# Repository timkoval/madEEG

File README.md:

# madEEG

This project is a fork and rebirth of an old project called "[OpenEEG](http://openeeg.sourceforge.net/doc/)".

The main feature of this project is that it uses currently available SMD components. Moreover, in the future I'm planning to try to make it cheaper using DSP instead of amplifier filters where it is possible.

I wanted to make it myself as a pet project, but unfortunately I don't have enough time and money. However, I really want this project to be developed... You are welcome to contribute!

## Requirements and tools

Schematic and PCB - [KiCAD](https://kicad-pcb.org/) 

Firmware - [STM32CubeIDE](https://www.st.com/en/development-tools/stm32cubeide.html) or any other IDE/code editor (As for me, I've recently migrated from CubeIDE to [VSCodium](https://vscodium.com/))

 Software - haven't thought about it yet, open to suggestions.

## Installation

No need to install project, just clone it, develop and contribute :) 

## Contributing

Pull requests are welcome! For major changes, please open an issue first to discuss what you would like to change.

## Authors

- **Tim Koval** - *Initial work* - [madTRACER](https://github.com/madTRACER)

## License

This project is under the MIT license.

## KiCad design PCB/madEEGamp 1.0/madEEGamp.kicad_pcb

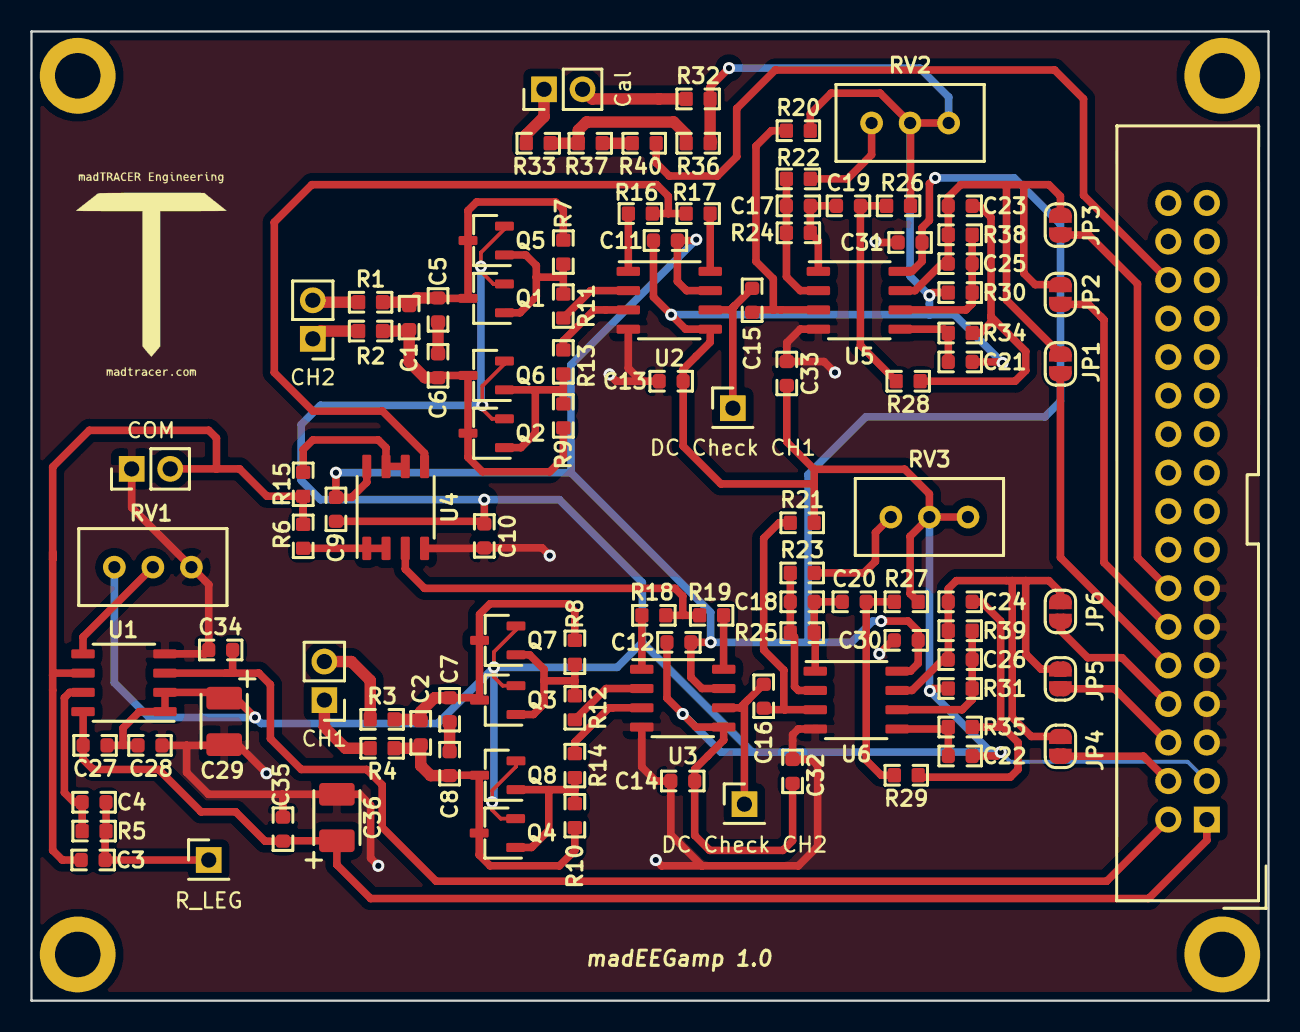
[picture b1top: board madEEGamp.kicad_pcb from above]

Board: 2 copper layers, 81.5 x 63.9 mm, 107 parts (0 on the bottom side), 66 nets.

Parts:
C1, C2: 10pF; C_0603
C3, C4, C17, C18, C25, C26: 1nF; C_0603
C5, C6, C7, C8: 100pF; C_0603
C9, C10, C11, C12, C13, C14, C27, C28, C30, C31, C32, C33: 100nF; C_0603
C15, C16, C19, C20: 1μF; C_0603
C21, C22: 220nF 5%; C_0603
C23, C24: 33nF 5%; C_0603
C29: 47μF tan 1ohm; CP_EIA-3528-15_AVX-H
C34, C35: 10nF; C_0603
C36: 47μF; CP_EIA-3528-15_AVX-H
CH1: CH1; PinHeader_1x02_P2.54mm_Vertical
CH2: CH2; PinHeader_1x02_P2.54mm_Vertical
COM: COM; PinHeader_1x02_P2.54mm_Vertical
Cal: Cal; PinHeader_1x02_P2.54mm_Vertical
DC Check CH1: DC Check CH1; PinHeader_1x01_P2.54mm_Vertical
DC Check CH2: DC Check CH2; PinHeader_1x01_P2.54mm_Vertical
JP1, JP4: SJ201; SolderJumper-2_P1.3mm_Open_RoundedPad1.0x1.5mm
JP2, JP5: SJ202; SolderJumper-2_P1.3mm_Open_RoundedPad1.0x1.5mm
JP3, JP6: SJ203; SolderJumper-2_P1.3mm_Open_RoundedPad1.0x1.5mm
Q1, Q2, Q3, Q4: BC847; SOT-23
Q5, Q6, Q7, Q8: BC857; SOT-23
R1, R2, R3, R4, R7, R8, R9, R10, R11, R12, R13, R14, R16, R17, R18, R19: 2k2; R_0603
R5: 200k; R_0603
R6, R15, R28, R29, R32, R33: 10k; R_0603
R20, R21, R26, R27, R37, R40: 1M; R_0603
R22, R23: 1k; R_0603
R24, R25, R38, R39: 100k; R_0603
R30, R31: 8.2k; R_0603
R34, R35: 15k; R_0603
R36: 100; R_0603
RV1, RV2, RV3: 20k; BOURNS_3296W_Vertical
R_LEG: R_LEG; PinHeader_1x01_P2.54mm_Vertical
U1, U4, U5, U6: AD822; SOIC-8_3.9x4.9mm_P1.27mm
U2, U3: AD620; SOIC-8_3.9x4.9mm_P1.27mm
X7: PIN_HEADER_2X17_2.54; IDC-Header_2x17_P2.54mm_Vertical

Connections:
+5V: C9.2, C11.1, C12.1, C30.1, C31.1, U2.7, U3.7, U4.8, U5.8, U6.8
/ADIN0: C24.1, C26.1, JP4.2, JP5.2, JP6.2, R39.1, U6.7
/ADIN1: C23.1, C25.1, JP1.2, JP2.2, JP3.2, R38.1, U5.7
/CH1+: CH1.1, R4.2
/CH1-: CH1.2, R3.2
/CH2+: CH2.1, R2.2
/CH2-: CH2.2, R1.1
/PWM: R40.1, X7.30
/R_LEG: C3.2, C4.2, R5.2, R_LEG.1
/VGND: C9.1, C10.1, C11.2, C12.2, C13.2, C14.2, C21.2, C22.2, C27.2, C28.2, C29.1, C32.1, C33.1, Q1.2, Q2.2, Q3.2, Q4.2, Q5.2, Q6.2, Q7.2, Q8.2, R20.2, R21.2, R26.2, R27.2, R30.2, R31.2, R32.1, R36.1, RV1.1, RV2.2, RV2.3, RV3.2, RV3.3, U1.1, U1.2, U2.5, U3.5, X7.3
GNDA: C10.2, C13.1, C14.1, C28.1, C29.2, C30.2, C31.2, C32.2, C33.2, C34.2, C35.2, C36.2, COM.1, RV1.3, U1.4, U2.4, U3.4, U4.4, U5.4, U6.4, X7.5, X7.7, X7.9, X7.11, X7.13
unnamed: C1.1, C5.1, Q1.3, Q5.3, R1.2, R7.1
unnamed: C1.2, C6.2, Q2.3, Q6.3, R2.1, R9.2
unnamed: C2.1, C7.1, Q3.3, Q7.3, R3.1, R8.2
unnamed: C2.2, C8.2, Q4.3, Q8.3, R4.1, R10.2
unnamed: C3.1, COM.2, R6.2, R15.2, U1.6
unnamed: C4.1, R5.1, U1.7
unnamed: C5.2, C6.1
unnamed: C7.2, C8.1
unnamed: C15.1, R20.1, U5.3
unnamed: C15.2, DC Check CH1.1, U2.6
unnamed: C16.1, R21.1, U6.3
unnamed: C16.2, DC Check CH2.1, U3.6
unnamed: C17.1, R22.1, R24.2, U5.2
unnamed: C17.2, C19.2, R24.1, U5.1
unnamed: C18.1, R23.1, R25.2, U6.2
unnamed: C18.2, C20.2, R25.1, U6.1
unnamed: C19.1, R26.1, R28.2
unnamed: C20.1, R27.1, R29.2
unnamed: C21.1, R34.1, U5.5
unnamed: C22.1, R35.1, U6.5
unnamed: C23.2, R28.1, R34.2
unnamed: C24.2, R29.1, R35.2
unnamed: C25.2, R30.1, R38.2, U5.6
unnamed: C26.2, R31.1, R39.2, U6.6
unnamed: C27.1, C35.1, C36.1, U1.8, X7.1
unnamed: C34.1, U1.3, X7.2
unnamed: JP1.1, X7.10
unnamed: JP2.1, X7.12
unnamed: JP3.1, X7.14
unnamed: JP4.1, X7.4
unnamed: JP5.1, X7.6
unnamed: JP6.1, X7.8
unnamed: Q1.1, Q5.1, R7.2, R11.2
unnamed: Q2.1, Q6.1, R9.1, R13.2
unnamed: Q3.1, Q7.1, R8.1, R12.2
unnamed: Q4.1, Q8.1, R10.1, R14.2
unnamed: R6.1, U4.1, U4.2
unnamed: R11.1, U2.2
unnamed: R12.1, U3.2
unnamed: R13.1, U2.3
unnamed: R14.1, U3.3
unnamed: R15.1, U4.6, U4.7
unnamed: R16.1, U2.1
unnamed: R16.2, R17.2, U4.5
unnamed: R17.1, U2.8
unnamed: R18.1, U3.1
unnamed: R18.2, R19.2, U4.3
unnamed: R19.1, U3.8
unnamed: R22.2, RV2.1
unnamed: R23.2, RV3.1
unnamed: Cal.2, R32.2
unnamed: R33.1, R36.2, R37.2
unnamed: Cal.1, R33.2
unnamed: R37.1, R40.2
unnamed: RV1.2, U1.5

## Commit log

2019-03-26 Initial commit (ampPCB draft)
2019-03-27 Test points added
2019-03-27 Fixed unrouted track
2020-01-07 Project reborn! =]
2020-01-12 madEEGamp 1.0 finished
2020-01-12 Ineractive BOM and Gerbers added for madEEGamp 1.0
